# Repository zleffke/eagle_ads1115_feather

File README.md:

# eagle_ads1115_feather
ADS1115 Featherwing EagleCAD design

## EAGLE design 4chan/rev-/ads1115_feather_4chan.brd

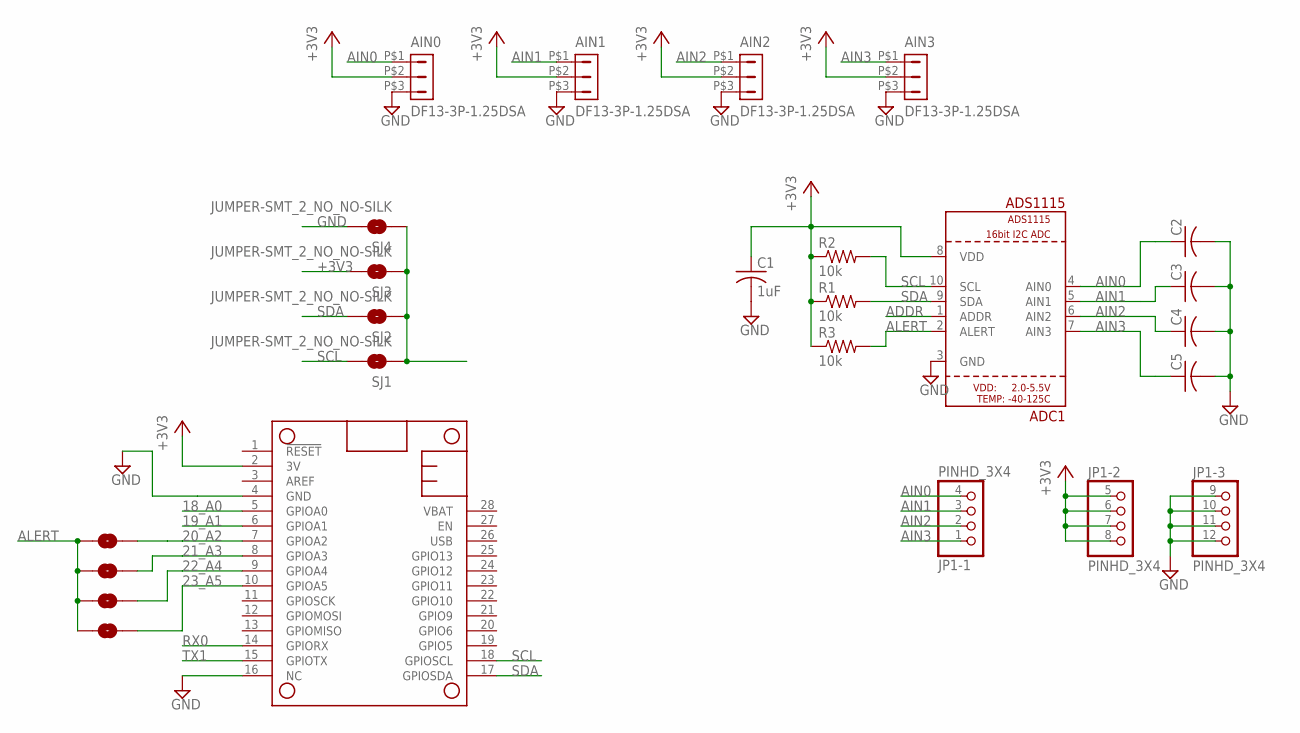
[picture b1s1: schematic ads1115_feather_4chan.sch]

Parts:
ADC1: ADS1115; MSOP10
AIN0, AIN1, AIN2, AIN3: DF13-3P-1.25DSA
C1: 1uF; C0805K
C2, C3, C4, C5: C-USC0805K; C0805K
JP1: PINHD_3X4; 3X4
MS1: FEATHERWING
R1, R2, R3: 10k; R0805
SJ1, SJ2, SJ3, SJ4, SJ5, SJ6, SJ7, SJ8: JUMPER-SMT_2_NO_NO-SILK; SMT-JUMPER_2_NO_NO-SILK

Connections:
18_A0: MS1.5 (GPIOA0)
19_A1: MS1.6 (GPIOA1)
20_A2: MS1.7 (GPIOA2), SJ7.2
21_A3: MS1.8 (GPIOA3), SJ6.2
22_A4: MS1.9 (GPIOA4), SJ5.2
23_A5: MS1.10 (GPIOA5), SJ8.2
+3V3: ADC1.8 (VDD), AIN0.P$2 (2), AIN1.P$2 (2), AIN2.P$2 (2), AIN3.P$2 (2), C1.1, JP1.5 (1), JP1.6 (2), JP1.7 (3), JP1.8 (4), MS1.2 (3V), R1.1, R2.1, R3.1, SJ3.2
ADDR: ADC1.1 (ADDR), SJ1.1, SJ2.1, SJ3.1, SJ4.1
AIN0: ADC1.4 (AIN0), AIN0.P$1 (1), C2.1, JP1.4
AIN1: ADC1.5 (AIN1), AIN1.P$1 (1), C3.1, JP1.3
AIN2: ADC1.6 (AIN2), AIN2.P$1 (1), C4.1, JP1.2
AIN3: ADC1.7 (AIN3), AIN3.P$1 (1), C5.1, JP1.1
ALERT: ADC1.2 (ALERT), R3.2, SJ5.1, SJ6.1, SJ7.1, SJ8.1
GND: ADC1.3 (GND), AIN0.P$3 (3), AIN1.P$3 (3), AIN2.P$3 (3), AIN3.P$3 (3), C1.2, C2.2, C3.2, C4.2, C5.2, JP1.9 (1), JP1.10 (2), JP1.11 (3), JP1.12 (4), MS1.4 (GND), MS1.16 (NC), SJ4.2
RX0: MS1.14 (GPIORX)
SCL: ADC1.10 (SCL), MS1.18 (GPIOSCL), R2.2, SJ1.2
SDA: ADC1.9 (SDA), MS1.17 (GPIOSDA), R1.2, SJ2.2
TX1: MS1.15 (GPIOTX)

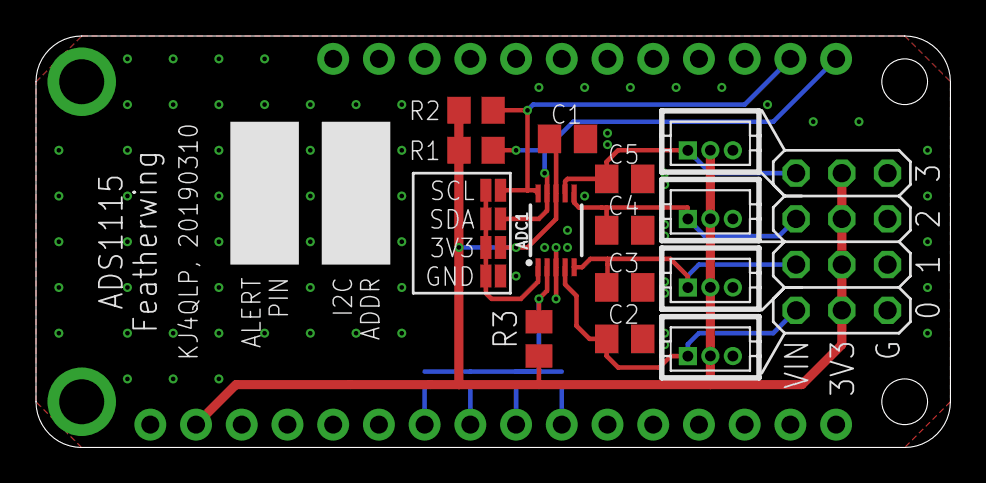
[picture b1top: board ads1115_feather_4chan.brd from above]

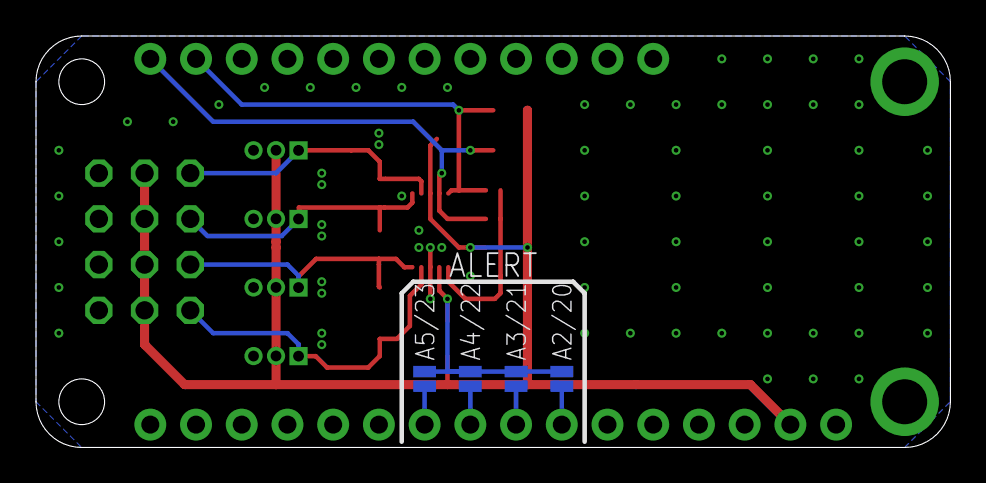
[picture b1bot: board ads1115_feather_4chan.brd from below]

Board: 2 copper layers, 50.8 x 22.9 mm, 23 parts (4 on the bottom side), 14 nets.

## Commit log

2019-03-10 added gitignore
2019-03-10 completed rev- version. Ordered from Osh Park.

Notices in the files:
parts and their libraries:
SparkFun-Jumpers: Licensing: Creative Commons ShareAlike 4.0 International - https://creativecommons.org/licenses/by-sa/4.0
